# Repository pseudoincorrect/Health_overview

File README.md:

<h1 align="center">Health Overview</h1>

<p align="center">

&nbsp;&nbsp;&nbsp;&nbsp;&nbsp;&nbsp;

</p>
<br>

# Description
The goal of Health Overview is to provide a Online (web) realtime overview of the health status of a group of individuals within a mesh RF network and send notifivations to users (watch-wearers and physicians) in case of an alarming health status, especially regarding dehydration. 
<br>
<br>
This system does not replace the examination of a physician and simply provides early health updates/warnings depending of vital signs, for later examination by a professional.
<br>
<br>

# Details
This project being a full IoT system stack, is split into 5 parts:
- Printed Circuit Board
- 3 Embedded Firmware (mesh nodes, mesh relays and mesh gateway)
- Python application for the gateway single board computer
- Backend application to be deployed on a cloud provider 
- Frontend Web application

<br>

## Disclamers
This project is not recommended for a new design starting point. We then moved to a LoraWan architecture for improved security and deployment ease. For an improved PCB design usable in a mesh network based on NRF52, the <a href="https://github.com/pseudoincorrect/smart_mask/tree/master/PCB">FlexySense project</a> is more recent and has been greatly improved. 
<br>
<br>
Also, being one of my "junior projects", its code needs improvement. Still, the demonstration was a success and all features were working properly. It enabled us to move on a next iteration with improved performances, reliability and security.
<br>
<br>
This project is kept as an archive (not maintened anymore), initialy on 5 differents private repositories, they have been merged for convenience and public access.
<br>
<br>

# Printed Circuit Board
The PCB has been designed with eagle on two layers. It includes a Nordic nrf52 module, temperature sensors, Heart-rate sensor, power supply/regulators, vibration motor, LEDs. for an improved design (but without heart rate sensor), please check the <a href="https://github.com/pseudoincorrect/smart_mask">FlexySense project</a>.

PCB Cad design files <a href="https://github.com/pseudoincorrect/Health_overview/tree/master/Overview_watch_pcb/Eagle/overview">here</a>.

<br>

<p align="center">

&nbsp;&nbsp;&nbsp;&nbsp;&nbsp;&nbsp;

<br>
<br>(From left to right) Eagle design, Debug board for testing, Prototype Smartwatch board
</p>

<br>

# 3 Embedded Firmware: (1) mesh smartwatch, (2) mesh relays and (3) mesh gateway
Health Overview is a system partly based on OpenThread mesh network, implemented on NordiSemi devices (nrf52).
<br>
Vital signs Data where gathered on the smartmatches (1), then data packets where relayed by the relay nodes (2) to the gateway node (3) that is serving as bridge between the mesh network and the cloud application.
<br>
<br>

<p align="center">

<br><br> Architecture of Health Overview
</p>

The wristwatch Overview_firmware/ folder contain the source code for the 3 systems (smartwatches, relays and gateway). each system has one folder for its specific code and share a common/ folder for system independant code.
<br>
More details <a href="https://github.com/pseudoincorrect/Health_overview/tree/master/Overview_firmware">here</a>.
<br>
<br>

# Python application for the gateway 
The gateway is the system that receive the data from the smartwatches and send them to the cloud application. Being a bidirection link, it can also send data from the could application to the smartwatches. the connection with cloud application is secured by a symetric key. 
<br>
<br>
The gateway is composed of 2 devices: a NRF52 development kit and a raspberry pi. 
- The NRF52 dev kit receive the data from the smartwaches and relay them to the raspberry py thanks to a serial connection. 
- The raspberry pi handle all the cloud related operations with a Python application.

More details <a href="https://github.com/pseudoincorrect/Health_overview/tree/master/Overview_gateway">here</a>.
<br>

<p align="center">

<br><br> Health Overview Gateway (link between smartwatches and cloud application)
</p>

<br>

# Backend stack to be deployed on a cloud provider 

The backend takes care of user management, devices management and health data storage.
It follow the MEAN stack (MongoDB, Express, Angular, NodeJs). When the application was active, it was deployed on Heroku. We then moved to a dockerised application on the next iteration of this project.

More details <a href="https://github.com/pseudoincorrect/Health_overview/tree/master/Overview_backend">here</a>.

<br>
<p align="center">

<br><br> Stack used for this project
</p>

<br>

# Frontend Web application
Data presentation was realized with an Angular single page application. Users could login and display the sensor of their group as well as displaying a detailed version of each smartwatch. Notification where displayed depending on the status of each sensor and notification could be sent to each wristwatch. The notification service was made with socketIo while all the data and login was made with HTTP.
 
 More details <a href="https://github.com/pseudoincorrect/Health_overview/tree/master/Overview_frontend">here</a>.

<br>

<p align="center">

&nbsp;&nbsp;&nbsp;&nbsp;&nbsp;&nbsp;

<br>
<br>Data from these screenshot are simulated to avoid sharing health data
</p>

#

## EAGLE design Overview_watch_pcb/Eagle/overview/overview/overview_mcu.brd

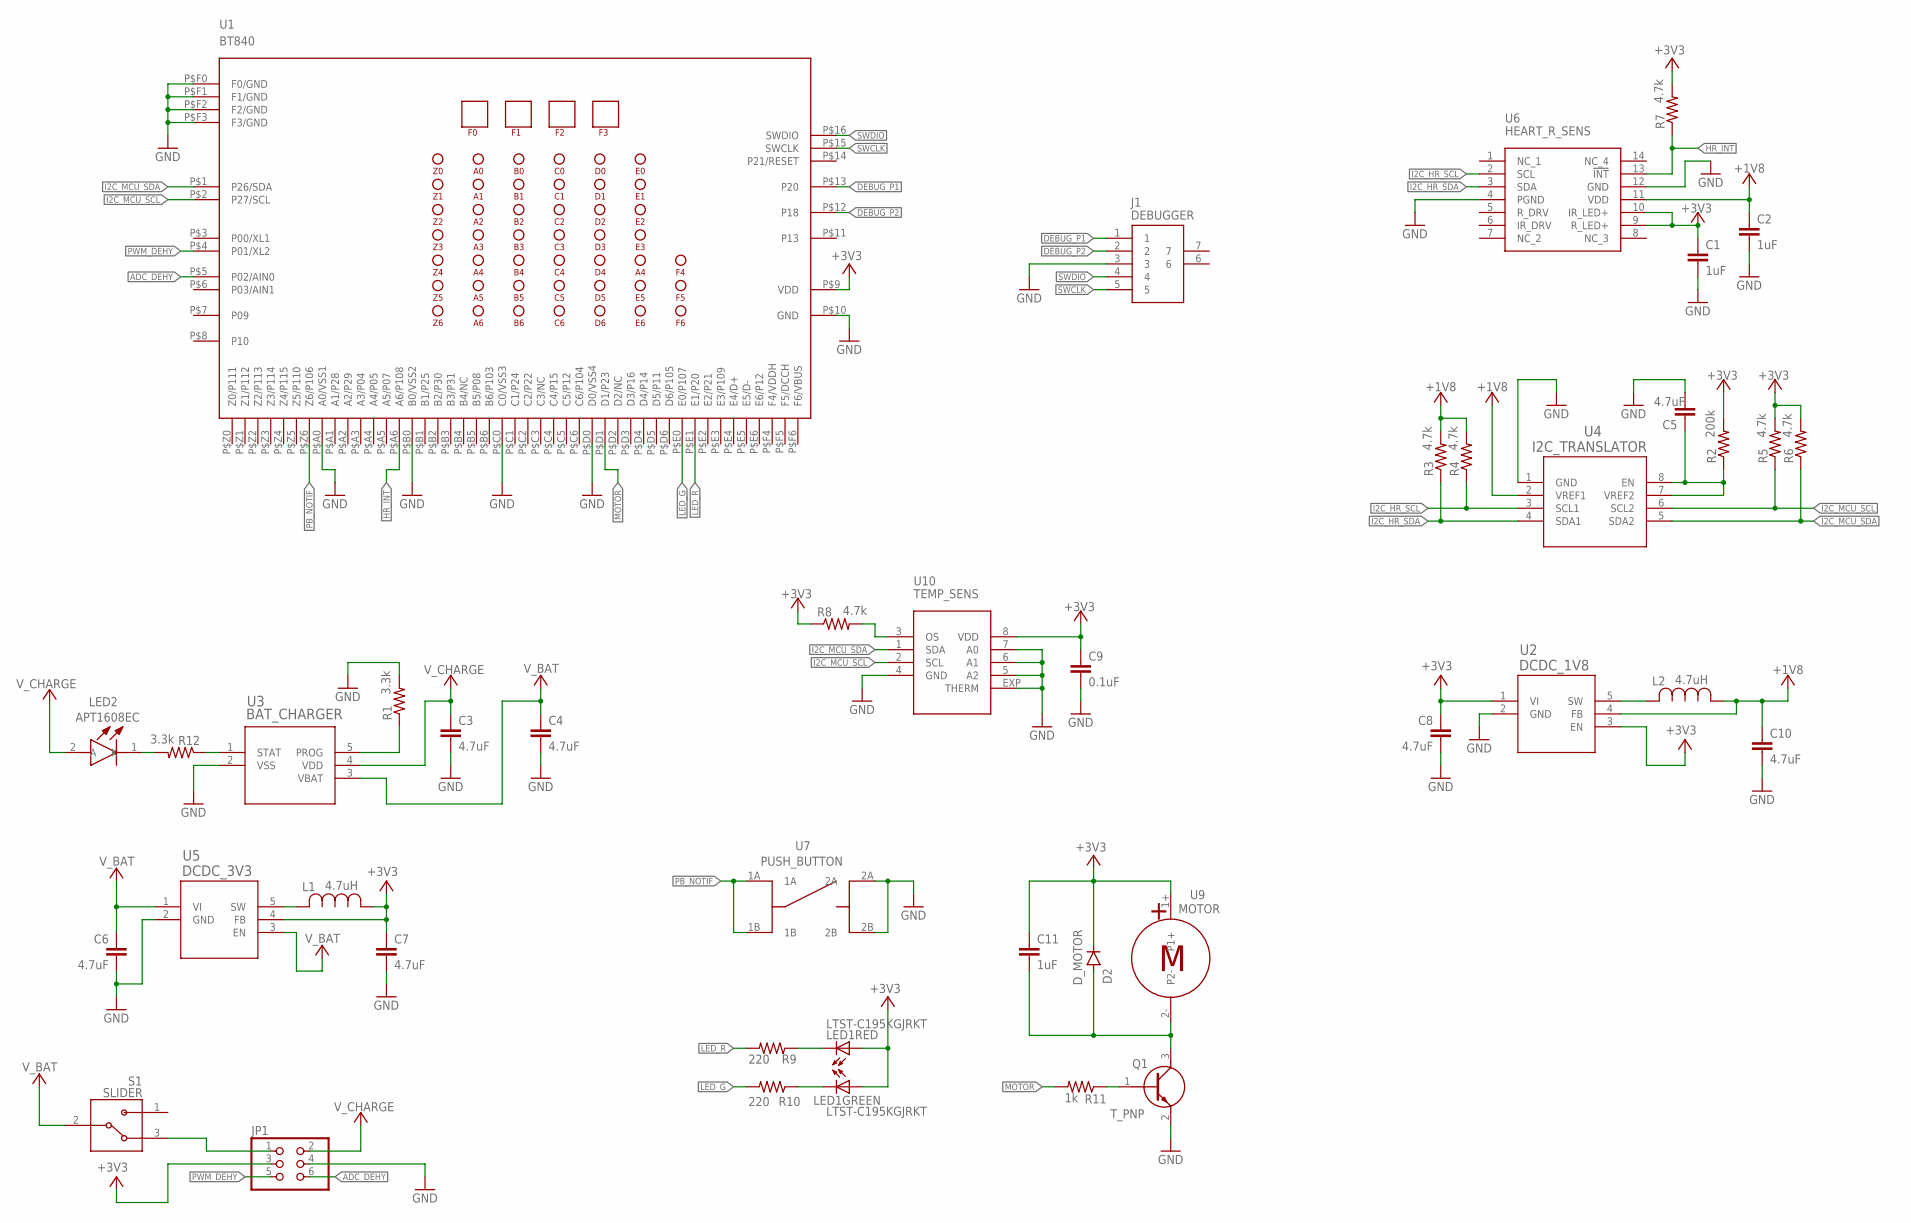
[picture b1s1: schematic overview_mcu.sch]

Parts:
C1, C2, C11: 1uF; C0402K
C3, C4, C5, C6, C7, C8, C10: 4.7uF; C0402K
C9: 0.1uF; C0402K
D2: D_MOTOR; SOD-123_MINI-SMA
J1: DEBUGGER; 0512810594
JP1: PINHD-2X3; 2X03
L1, L2: 4.7uH; IND_1608
LED1: LTST-C195KGJRKT; LED-SMT
LED2: APT1608EC; LEDC1608X85N
Q1: T_PNP; SOT95P240X93-3N
R1, R12: 3.3k; R0402
R2: 200k; R0402
R3, R4, R5, R6, R7, R8: 4.7k; R0402
R9, R10: 220; R0402
R11: 1k; R0402
S1: SLIDER; SW_CJS-1200TA
U1: BT840
U2: DCDC_1V8; DBV5
U3: BAT_CHARGER; SOT-23-5_MC
U4: I2C_TRANSLATOR; DQE8
U5: DCDC_3V3; DBV5
U6: HEART_R_SENS; MAX30102
U7: PUSH_BUTTON
U9: MOTOR
U10: TEMP_SENS; MAX30205

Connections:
+1V8: C2.1, C10.1, L2.1, R3.2, R4.2, U2.4 (FB), U4.2 (VREF1), U6.11 (VDD)
+3V3: C1.1, C7.1, C8.1, C9.1, C11.1, D2.C, JP1.3, L1.1, LED1.P$1 (A), LED1.P$2 (A), R2.2, R5.2, R6.2, R7.2, R8.1, U1.P$9 (VDD), U2.1 (VI), U2.3 (EN), U5.4 (FB), U6.9 (R_LED+), U6.10 (IR_LED+), U9.1+, U10.8 (VDD)
ADC_DEHY: JP1.6, U1.P$5 (P02/AIN0)
DEBUG_P1: J1.1, U1.P$13 (P20)
DEBUG_P2: J1.2, U1.P$12 (P18)
GND: C1.2, C2.2, C3.2, C4.2, C5.2, C6.2, C7.2, C8.2, C9.2, C10.2, J1.3, JP1.4, Q1.2 (E), R1.2, U1.P$10 (GND), U1.P$A0 (A0/VSS1), U1.P$B0 (B0/VSS2), U1.P$C0 (C0/VSS3), U1.P$D0 (D0/VSS4), U1.P$F0 (F0/GND), U1.P$F1 (F1/GND), U1.P$F2 (F2/GND), U1.P$F3 (F3/GND), U2.2 (GND), U3.2 (VSS), U4.1 (GND), U5.2 (GND), U6.4 (PGND), U6.12 (GND), U7.2A, U7.2B, U10.4 (GND), U10.5 (A2), U10.6 (A1), U10.7 (A0), U10.EXP (THERM)
HR_INT: R7.1, U1.P$A6 (A6/P108), U6.13 (!INT)
I2C_HR_SCL: R4.1, U4.3 (SCL1), U6.2 (SCL)
I2C_HR_SDA: R3.1, U4.4 (SDA1), U6.3 (SDA)
I2C_MCU_SCL: R5.1, U1.P$2 (P27/SCL), U4.6 (SCL2), U10.2 (SCL)
I2C_MCU_SDA: R6.1, U1.P$1 (P26/SDA), U4.5 (SDA2), U10.1 (SDA)
LED_G: R10.2, U1.P$E0 (E0/P107)
LED_R: R9.2, U1.P$E1 (E1/P20)
MOTOR: R11.2, U1.P$D1 (D1/P23)
unnamed: JP1.1, S1.3
unnamed: R1.1, U3.5 (PROG)
unnamed: C5.1, R2.1, U4.7 (VREF2), U4.8 (EN)
unnamed: L1.2, U5.5 (SW)
unnamed: L2.2, U2.5 (SW)
unnamed: LED1.P$4 (C), R9.1
unnamed: R8.2, U10.3 (OS)
unnamed: LED1.P$3 (C), R10.1
unnamed: R12.1, U3.1 (STAT)
unnamed: LED2.1 (K), R12.2
unnamed: C11.2, D2.A, Q1.3 (C), U9.2-
unnamed: Q1.1 (B), R11.1
PB_NOTIF: U1.P$Z6 (Z6/P106), U7.1A, U7.1B
PWM_DEHY: JP1.5, U1.P$4 (P01/XL2)
SWCLK: J1.5, U1.P$15 (SWCLK)
SWDIO: J1.4, U1.P$16 (SWDIO)
V_BAT: C4.1, C6.1, S1.2, U3.3 (VBAT), U5.1 (VI), U5.3 (EN)
V_CHARGE: C3.1, JP1.2, LED2.2 (A), U3.4 (VDD)

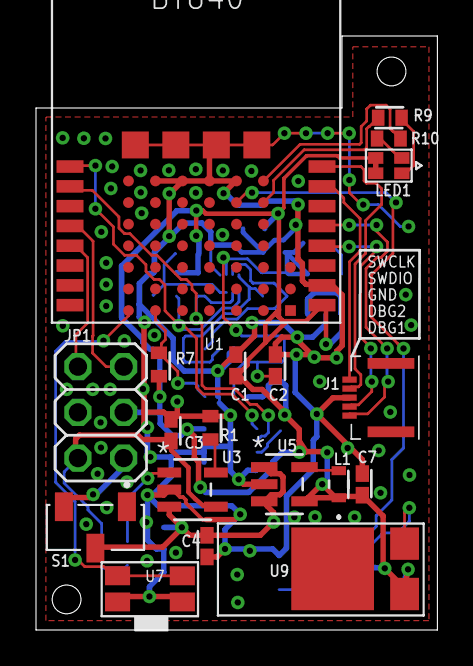
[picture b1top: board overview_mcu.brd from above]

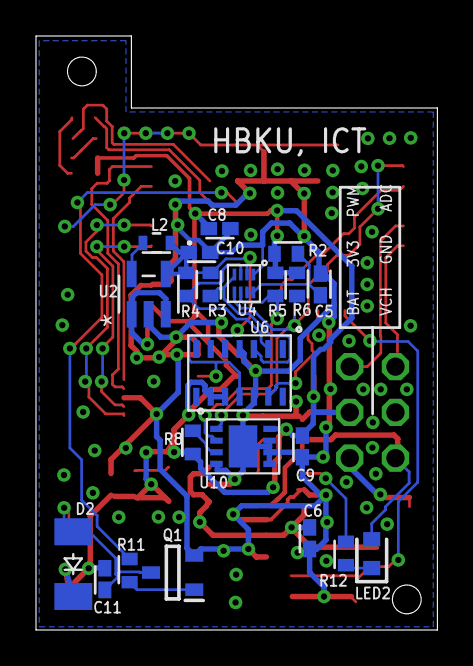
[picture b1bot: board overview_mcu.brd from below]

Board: 2 copper layers, 22.3 x 33.0 mm, 41 parts (22 on the bottom side), 32 nets.

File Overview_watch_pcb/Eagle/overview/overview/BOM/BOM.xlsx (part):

| PART | VALUE | DEVICE | PACKAGE | DESCRIPTION | LINK | MANUFACTURER | MANUFACTURER_PART | VENDOR_PART | VENDOR | QUANTITY
1 | C1 | 1uF | C-EUC0402K | C0402K | CAP CER 1UF 6.3V X5R 0402 | https://www.digikey.com/product-detail/en/yageo/CC0402KRX5R5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 | Yageo | CC0402KRX5R5BB105 | 311-1438-1-ND | digikey.com | 1
2 | C2 | 1uF | C-EUC0402K | C0402K | CAP CER 1UF 6.3V X5R 0402 | https://www.digikey.com/product-detail/en/yageo/CC0402KRX5R5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 | Yageo | CC0402KRX5R5BB105 | 311-1438-1-ND | digikey.com | 1
3 | C3 | 4.7uF | C-EUC0402K | C0402K | CAP CER 4.7PF 50V C0G/NPO 0402 | https://www.digikey.com/product-detail/en/yageo/CC0402CRNPO9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 | Yageo | CC0402CRNPO9BN4R7 | 311-1367-1-ND | digikey.com | 1
4 | C4 | 4.7uF | C-EUC0402K | C0402K | CAP CER 4.7PF 50V C0G/NPO 0402 | https://www.digikey.com/product-detail/en/yageo/CC0402CRNPO9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 | Yageo | CC0402CRNPO9BN4R7 | 311-1367-1-ND | digikey.com | 1
5 | C5 | 4.7uF | C-EUC0402K | C0402K | CAP CER 4.7PF 50V C0G/NPO 0402 | https://www.digikey.com/product-detail/en/yageo/CC0402CRNPO9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 | Yageo | CC0402CRNPO9BN4R7 | 311-1367-1-ND | digikey.com | 1
6 | C6 | 4.7uF | C-EUC0402K | C0402K | CAP CER 4.7PF 50V C0G/NPO 0402 | https://www.digikey.com/product-detail/en/yageo/CC0402CRNPO9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 | Yageo | CC0402CRNPO9BN4R7 | 311-1367-1-ND | digikey.com | 1
7 | C7 | 4.7uF | C-EUC0402K | C0402K | CAP CER 4.7PF 50V C0G/NPO 0402 | https://www.digikey.com/product-detail/en/yageo/CC0402CRNPO9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 | Yageo | CC0402CRNPO9BN4R7 | 311-1367-1-ND | digikey.com | 1
8 | C8 | 4.7uF | C-EUC0402K | C0402K | CAP CER 4.7PF 50V C0G/NPO 0402 | https://www.digikey.com/product-detail/en/yageo/CC0402CRNPO9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 | Yageo | CC0402CRNPO9BN4R7 | 311-1367-1-ND | digikey.com | 1
9 | C9 | 0.1uF | C-EUC0402K | C0402K | CAP CER 0.1UF 25V Y5V 0402 | https://www.digikey.com/product-detail/en/yageo/CC0402ZRY5V8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 | Yageo | CC0402ZRY5V8BB104 | 311-1375-1-ND | digikey.com | 1
10 | C10 | 4.7uF | C-EUC0402K | C0402K | CAP CER 4.7PF 50V C0G/NPO 0402 | https://www.digikey.com/product-detail/en/yageo/CC0402CRNPO9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 | Yageo | CC0402CRNPO9BN4R7 | 311-1367-1-ND | digikey.com | 1
11 | C11 | 1uF | C-EUC0402K | C0402K | CAP CER 1UF 6.3V X5R 0402 | https://www.digikey.com/product-detail/en/yageo/CC0402KRX5R5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 | Yageo | CC0402KRX5R5BB105 | 311-1438-1-ND | digikey.com | 1
12 | D2 | D_MOTOR | 1N4148W-TP | SOD-123 | DIODE GEN PURP 100V 150MA SOD123 | https://www.digikey.com/product-detail/en/1N4148W-TP/1N4148W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 | Micro Commercial Co | 1N4148W-TP | 1N4148WTPMSCT-ND | digikey.com | 1
13 | J1 | DEBUGGER | DEBUGGER | 512810594 | CONN FFC FPC 5POS 0.50MM R/A | https://www.digikey.com/product-detail/en/molex-llc/05128105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 | Molex | 512810594 | WM12846CT-ND | digikey.com | 1
14 | L1 | 4.7uH | L_0604 | IND_1608 | FIXED IND 4.7UH 500MA 240 MOHM | https://www.digikey.com/product-detail/en/tdk-corporation/GL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 | TDK Corporation | GLFR1608T4R7M-LR | 445-3607-1-ND | digikey.com | 1
15 | L2 | 4.7uH | L_0604 | IND_1608 | FIXED IND 4.7UH 500MA 240 MOHM | https://www.digikey.com/product-detail/en/tdk-corporation/GL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 | TDK Corporation | GLFR1608T4R7M-LR | 445-3607-1-ND | digikey.com | 1
16 | LED1 | LTST-C195KGJRKT | LTST-C195KGJRKT | LED-SMT | LED GREEN/RED CLEAR CHIP SMD | https://www.digikey.com/product-detail/en/lite-on-inc/LTST-C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 | Lite-On Inc. | LTST-C195KGJRKT | 160-1452-1-ND | digikey.com | 1
17 | LED2 | APT1608EC | APT1608EC | 603 | LED RED CLEAR CHIP SMD | https://www.digikey.com/product-detail/en/kingbright/APT1608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 | Kingbright | APT1608EC | 754-1117-1-ND | digikey.com | 1
18 | Q1 | T_PNP | T_PNP | SOT95P240X93-3N | TRANS NPN 40V 0.2A SOT23 | https://www.digikey.com/products/en?keywords=MMBT3904TPMSCT | Micro Commercial Co | MMBT3904-TP | MMBT3904TPMSCT-ND | digikey.com | 1
19 | R1 | 3.3k | R-US_R0402 | R0402 | RES SMD 3.3K OHM 1% 1/16W 0402 | https://www.digikey.com/product-detail/en/yageo/RC0402FR-073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 | Yageo | RC0402FR-073K3L | 311-3.30KLRCT-ND | digikey.com | 1
20 | R2 | 200k | R-US_R0402 | R0402 | RES SMD 200K OHM 1% 1/16W 0402 | https://www.digikey.com/product-detail/en/yageo/RC0402FR-072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 | Yageo | RC0402FR-07200KL | 311-200KLRCT-ND | digikey.com | 1
21 | R3 | 4.7k | R-US_R0402 | R0402 | RES SMD 4.7K OHM 5% 1/16W 0402 | https://www.digikey.com/product-detail/en/yageo/RC0402JR-074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 | Yageo | RC0402JR-074K7L | 311-4.7KJRCT-ND | digikey.com | 1
22 | R4 | 4.7k | R-US_R0402 | R0402 | RES SMD 4.7K OHM 5% 1/16W 0402 | https://www.digikey.com/product-detail/en/yageo/RC0402JR-074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 | Yageo | RC0402JR-074K7L | 311-4.7KJRCT-ND | digikey.com | 1
23 | R5 | 4.7k | R-US_R0402 | R0402 | RES SMD 4.7K OHM 5% 1/16W 0402 | https://www.digikey.com/product-detail/en/yageo/RC0402JR-074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 | Yageo | RC0402JR-074K7L | 311-4.7KJRCT-ND | digikey.com | 1
24 | R6 | 4.7k | R-US_R0402 | R0402 | RES SMD 4.7K OHM 5% 1/16W 0402 | https://www.digikey.com/product-detail/en/yageo/RC0402JR-074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 | Yageo | RC0402JR-074K7L | 311-4.7KJRCT-ND | digikey.com | 1
25 | R7 | 4.7k | R-US_R0402 | R0402 | RES SMD 4.7K OHM 5% 1/16W 0402 | https://www.digikey.com/product-detail/en/yageo/RC0402JR-074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 | Yageo | RC0402JR-074K7L | 311-4.7KJRCT-ND | digikey.com | 1
26 | R8 | 4.7k | R-US_R0402 | R0402 | RES SMD 4.7K OHM 5% 1/16W 0402 | https://www.digikey.com/product-detail/en/yageo/RC0402JR-074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 | Yageo | RC0402JR-074K7L | 311-4.7KJRCT-ND | digikey.com | 1
27 | R9 | 220 | R-US_R0402 | R0402 | RES SMD 220 OHM 5% 1/16W 0402 | https://www.digikey.com/product-detail/en/yageo/RC0402JR-072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 | Yageo | RC0402JR-07220RL | 311-220JRCT-ND | digikey.com | 1
28 | R10 | 220 | R-US_R0402 | R0402 | RES SMD 220 OHM 5% 1/16W 0402 | https://www.digikey.com/product-detail/en/yageo/RC0402JR-072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 | Yageo | RC0402JR-07220RL | 311-220JRCT-ND | digikey.com | 1
29 | R11 | 1k | R-US_R0402 | R0402 | RES SMD 1K OHM 5% 1/16W 0402 | https://www.digikey.com/product-detail/en/yageo/RC0402JR-071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 | Yageo | RC0402JR-071KL | 311-1.0KJRCT-ND | digikey.com | 1
30 | R12 | 470 | R-US_R0402 | R0402 | RES SMD 470 OHM 5% 1/16W 0402 | https://www.digikey.com/product-detail/en/yageo/RC0402JR-074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 | Yageo | RC0402JR-07470RL | 311-470JRCT-ND | digikey.com | 1
31 | S1 | SLIDER | SLIDER | SW_CJS-1200TA | SWITCH SLIDE SPDT 100MA 6V | https://www.digikey.com/product-detail/en/nidec-copal-electr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 | Nidec Copal Electronics | CJS-1200TA | 563-1021-1-ND | digikey.com | 1
32 | U2 | DCDC_1V8 | DCDC_1V8 | DBV5 | IC REG BUCK 1.8V 0.3A SYNC SOT23 | https://www.digikey.com/product-detail/en/texas-instruments/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 | Texas Instruments | TPS62202DBVR | 296-16730-1-ND | digikey.com | 1
33 | U3 | BAT_CHARGER | BAT_CHARGER | SOT-23-5_MC | IC CONTROLLR LI-ION 4.2V SOT23-5 | https://www.digikey.com/product-detail/en/microchip-technolo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 | Microchip | MCP73831T2ACIOT | MCP73831T-2ACI/OTCT-ND | digikey.com | 1
34 | U4 | I2C_TRANSLATOR | I2C_TRANSLATOR | DQE8 | IC TRNSLTR BIDIRECTIONAL 8X2SON | https://www.digikey.com/product-detail/en/texas-instruments/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 | Texas Instruments | PCA9306DQER | 296-27957-1-ND | digikey.com | 1
35 | U5 | DCDC_3V3 | DCDC_3V3 | DBV5 | IC REG BUCK 3.3V 0.3A SYNC SOT23 | https://www.digikey.com/product-detail/en/texas-instruments/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 | Texas Instruments | TPS62203DBVR | 296-39452-1-ND | digikey.com | 1
36 | U6 | HEART_R_SENS | HEART_R_SENS | MAX30102 | IC SENSOR OXIMETER/HEARTRATE | https://www.digikey.com/product-detail/en/maxim-integrated/M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 | Maxim Integrated | MAX30102EFD+ | MAX30102EFD+-ND | digikey.com | 1
37 | U7 | PUSH_BUTTON | PUSH_BUTTON | PUSH_BUTTON | SWITCH TACTILE SPST-NO 0.05A 12V | https://www.digikey.com/product-detail/en/panasonic-electron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 | Panasonic Electronic Components | EVQ-P7A01P | P16763CT-ND | digikey.com | 1
38 | U9 | MOTOR | MOTOR | MOTOR | VIBRATION MOTOR CYL 2.7V SMD | https://www.digikey.com/product-detail/en/jinlong-machinery-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 | Jinlong Machinery & Electronics, Inc. | Z4FC1B1301781 | 1670-1011-1-ND | digikey.com | 1
39 | U10 | TEMP_SENS | TEMP_SENS | MAX30205 | SWITCH TACTILE SPST-NO 0.05A 12V | https://www.digikey.com/product-detail/en/maxim-integrated/M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 | Maxim Integrated | MAX30205MTA+ | MAX30205MTA+-ND | digikey.com | 1
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
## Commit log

2021-04-14 Initial archiving commit
2021-04-14 updated readmes
2021-04-15 typo readme

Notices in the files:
README.md:
License: MIT
